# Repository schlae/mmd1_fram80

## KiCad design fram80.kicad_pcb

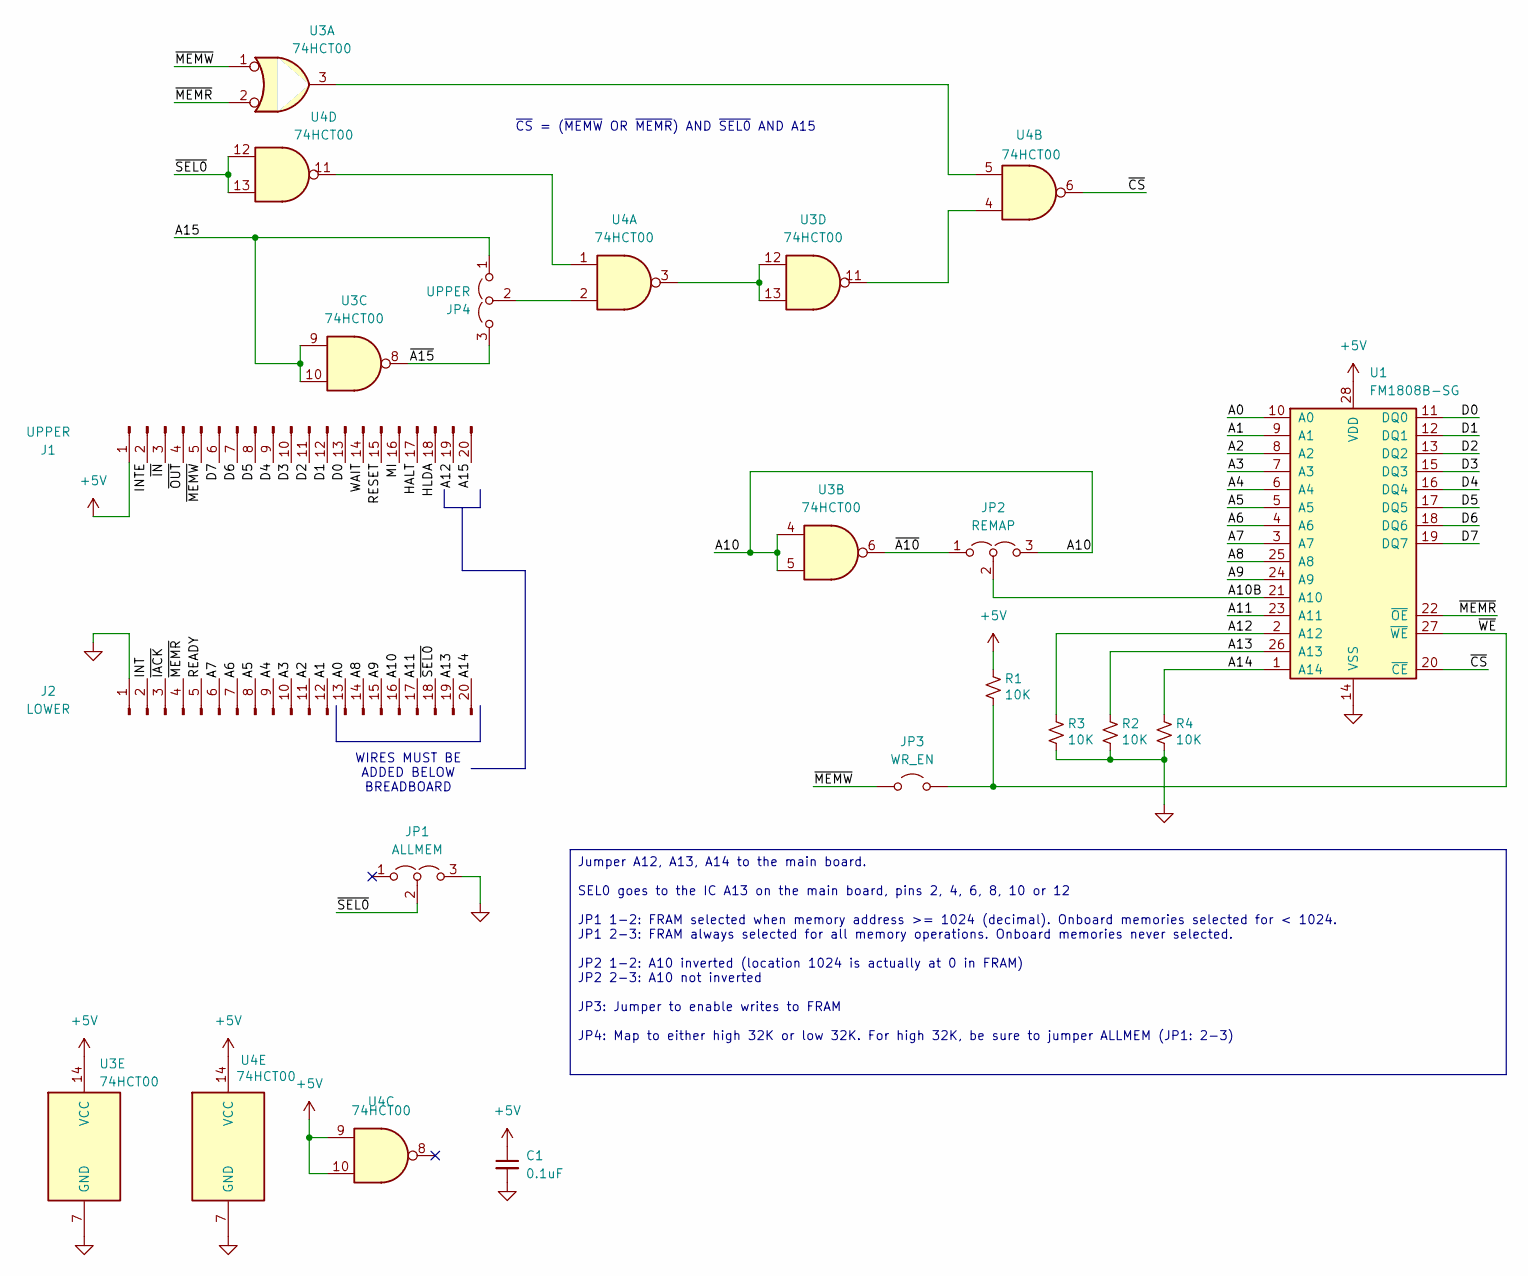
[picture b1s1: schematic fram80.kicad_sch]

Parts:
C1: 0.1uF; C_0805_2012Metric
J1: UPPER; 1544210-2_20
J2: LOWER; 1544210-2_20
JP1: ALLMEM; PinHeader_1x03_P2.54mm_Vertical
JP2: REMAP; PinHeader_1x03_P2.54mm_Vertical
JP3: WR_EN; PinHeader_1x02_P2.54mm_Vertical
JP4: UPPER; PinHeader_1x03_P2.54mm_Vertical
R1, R2, R3, R4: 10K; R_0805_2012Metric
U1: FM1808B-SG; SOIC-28W_7.5x17.9mm_P1.27mm
U3, U4: 74HCT00; TSSOP-14_4.4x5mm_P0.65mm

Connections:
+5V: C1.1, J1.1, R1.1, U1.28 (VDD), U3.14 (VCC), U4.9, U4.10, U4.14 (VCC)
/A0: J2.13, U1.10 (A0)
/A1: J2.12, U1.9 (A1)
/A2: J2.11, U1.8 (A2)
/A3: J2.10, U1.7 (A3)
/A4: J2.9, U1.6 (A4)
/A5: J2.8, U1.5 (A5)
/A6: J2.7, U1.4 (A6)
/A7: J2.6, U1.3 (A7)
/A8: J2.14, U1.25 (A8)
/A9: J2.15, U1.24 (A9)
/A10: J2.16, JP2.3 (B), U3.4, U3.5
/A10B: JP2.2 (C), U1.21 (A10)
/A11: J2.17, U1.23 (A11)
/A12: J1.19, R3.1, U1.2 (A12)
/A13: J2.19, R2.1, U1.26 (A13)
/A14: J2.20, R4.1, U1.1 (A14)
/A15: J1.20, JP4.1 (A), U3.9, U3.10
/D0: J1.13, U1.11 (DQ0)
/D1: J1.12, U1.12 (DQ1)
/D2: J1.11, U1.13 (DQ2)
/D3: J1.10, U1.15 (DQ3)
/D4: J1.9, U1.16 (DQ4)
/D5: J1.8, U1.17 (DQ5)
/D6: J1.7, U1.18 (DQ6)
/D7: J1.6, U1.19 (DQ7)
/HALT: J1.17
/HLDA: J1.18
/INT: J2.2
/INTE: J1.2
/MI: J1.16
/READY: J2.5
/RESET: J1.15
/WAIT: J1.14
/~A10: JP2.1 (A), U3.6
/~A15: JP4.3 (B), U3.8
/~CS: U1.20 (~CE), U4.6
/~IACK: J2.3
/~IN: J1.3
/~MEMR: J2.4, U1.22 (~OE), U3.2
/~MEMW: J1.5, JP3.1 (A), U3.1
/~OUT: J1.4
/~SEL0: J2.18, JP1.2 (C), U4.12, U4.13
/~WE: JP3.2 (B), R1.2, U1.27 (~WE)
GND: C1.2, J2.1, JP1.3 (B), R2.2, R3.2, R4.2, U1.14 (VSS), U3.7 (GND), U4.7 (GND)
unnamed: JP4.2 (C), U4.2
unnamed: U3.3, U4.5
unnamed: U3.11, U4.4
unnamed: U3.12, U3.13, U4.3
unnamed: U4.1, U4.11

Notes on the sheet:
WIRES MUST BE ADDED BELOW BREADBOARD
~{CS} = (~{MEMW} OR ~{MEMR}) AND ~{SEL0} AND A15
Jumper A12, A13, A14 to the main board. SEL0 goes to the IC A13 on the main board, pins 2, 4, 6, 8, 10 or 12 JP1 1-2: FRAM selected when memory address >= 1024 (decimal). Onboard memories selected for < 1024. JP1 2-3: FRAM always selected for all memory operations. Onboard memories never selected. 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

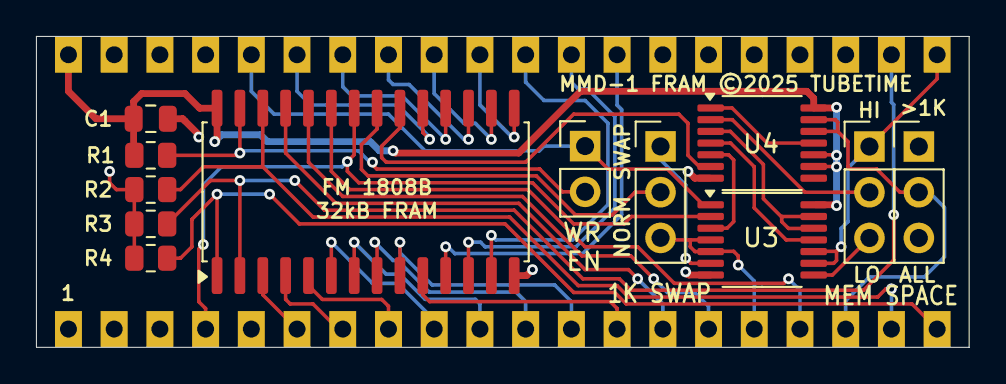
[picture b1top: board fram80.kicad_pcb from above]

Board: 2 copper layers, 51.8 x 17.3 mm, 14 parts (1 on the bottom side), 39 nets.

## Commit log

2025-07-18 Support upper 32K
2025-08-07 Fab out rev 2

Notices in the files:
fram80.kicad_pcb:
MMD-1 FRAM ©2025 TUBETIME
